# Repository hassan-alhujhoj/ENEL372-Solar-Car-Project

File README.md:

# ENEL372 - Solar Car Project

Ranking: $3^{rd}$ place

## Contributors
* [Hassan Alhujhoj](https://github.com/hassan-alhujhoj)
* [Abdul Azim Shafi]()
* [Azrif Fuad]()

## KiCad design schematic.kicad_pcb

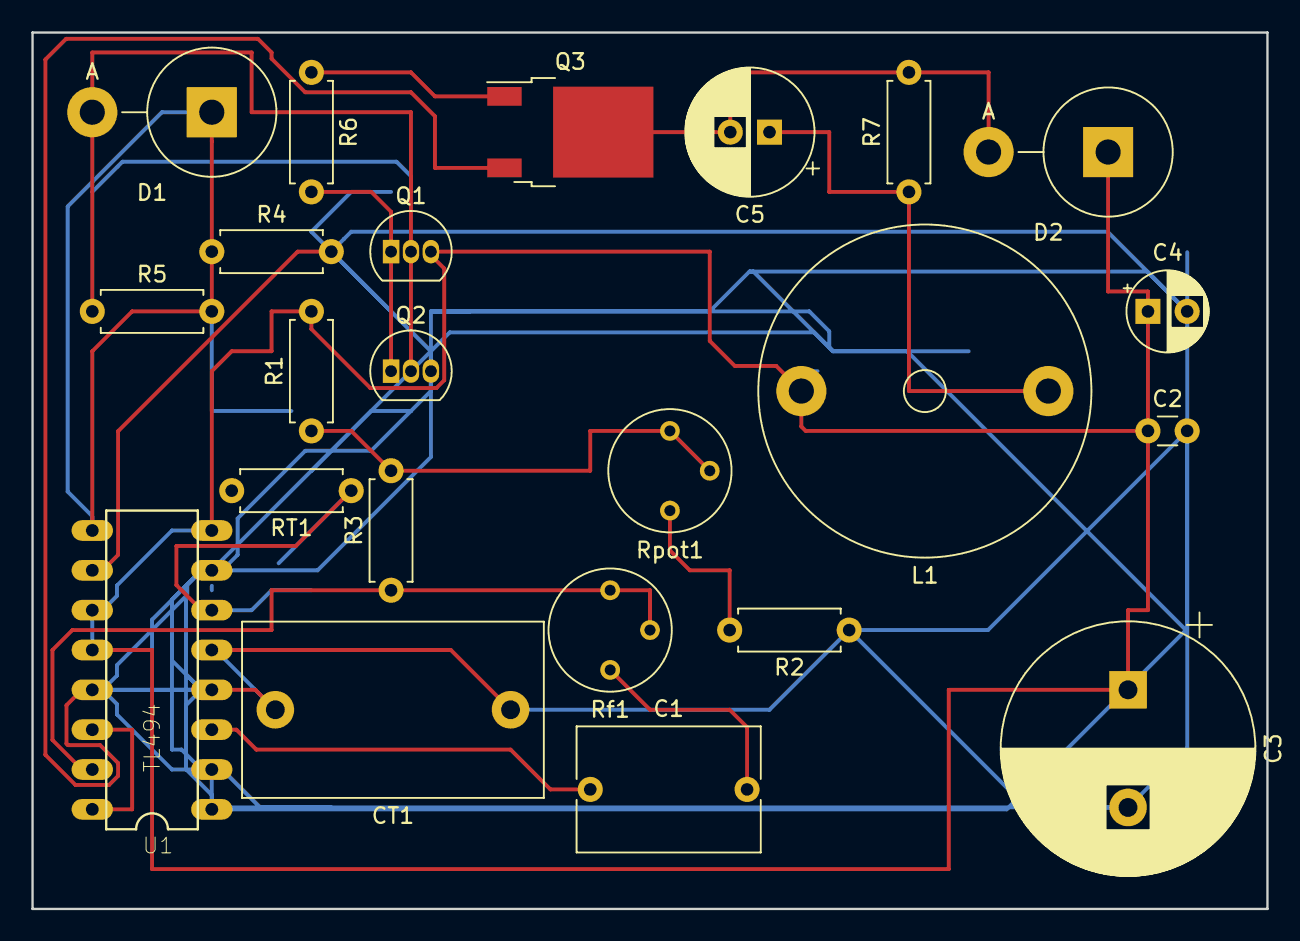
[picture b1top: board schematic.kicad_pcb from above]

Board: 2 copper layers, 78.7 x 55.9 mm, 23 parts (0 on the bottom side), 16 nets.

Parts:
C1: 1uF; C_Rect_L11.5mm_W7.8mm_P10.00mm_MKT
C2: 100nF; C_Disc_D3.0mm_W1.6mm_P2.50mm
C3: 330uF; CP_Radial_D16.0mm_P7.50mm
C4: 1uF; CP_Radial_D5.0mm_P2.50mm
C5: 9.4uF; CP_Radial_D8.0mm_P2.50mm
CT1: 10nF; C_Rect_L19.0mm_W11.0mm_P15.00mm_MKS4
D1, D2: Schottky; D_5KPW_P7.62mm_Vertical_AnodeUp
L1: 80uH; L_Radial_D21.0mm_P15.75mm_Vishay_IHB-2
Q1: 2N3904; TO-92_Inline
Q2: 2N3906; TO-92_Inline
Q3: IPP034N03L; TO-252-2
R1: 2k; R_Axial_DIN0207_L6.3mm_D2.5mm_P7.62mm_Horizontal
R2: 800; R_Axial_DIN0207_L6.3mm_D2.5mm_P7.62mm_Horizontal
R3: 100k; R_Axial_DIN0207_L6.3mm_D2.5mm_P7.62mm_Horizontal
R4: 8.33k; R_Axial_DIN0207_L6.3mm_D2.5mm_P7.62mm_Horizontal
R5: 1.415k; R_Axial_DIN0207_L6.3mm_D2.5mm_P7.62mm_Horizontal
R6: 15; R_Axial_DIN0207_L6.3mm_D2.5mm_P7.62mm_Horizontal
R7: 5; R_Axial_DIN0207_L6.3mm_D2.5mm_P7.62mm_Horizontal
RT1: 1.375k; R_Axial_DIN0207_L6.3mm_D2.5mm_P7.62mm_Horizontal
Rf1: 500k; Potentiometer_Bourns_3339P_Vertical
Rpot1: 200; Potentiometer_Bourns_3339P_Vertical
U1: TL494; DIL16

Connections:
unnamed: C1.1, U1.3
unnamed: C1.2, Rf1.3
unnamed: C2.1, C3.1, C4.1, D2.1, L1.2, Q1.3, R1.2, U1.8, U1.11, U1.12
unnamed: C2.2, C3.2, C4.2, CT1.1, Q2.3, Q3.3, R2.1, R4.2, RT1.1, U1.1, U1.2, U1.4, U1.7, U1.10, U1.13
unnamed: C5.1, L1.1, R7.1
unnamed: C5.2, D2.2, Q3.2, R7.2
unnamed: CT1.2, U1.5
unnamed: D1.1, R4.1, R5.2, U1.9
unnamed: D1.2, Q1.2, Q2.2, R5.1
unnamed: Q1.1, Q2.1, R6.2
unnamed: Q3.1, R6.1
unnamed: R1.1, R3.2, Rpot1.1, Rpot1.2
unnamed: R2.2, Rpot1.3
unnamed: R3.1, Rf1.1, Rf1.2, U1.15
unnamed: RT1.2, U1.6
unnamed: U1.14, U1.16

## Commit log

2020-09-20 Adding KiCad Schematic and PCB files
